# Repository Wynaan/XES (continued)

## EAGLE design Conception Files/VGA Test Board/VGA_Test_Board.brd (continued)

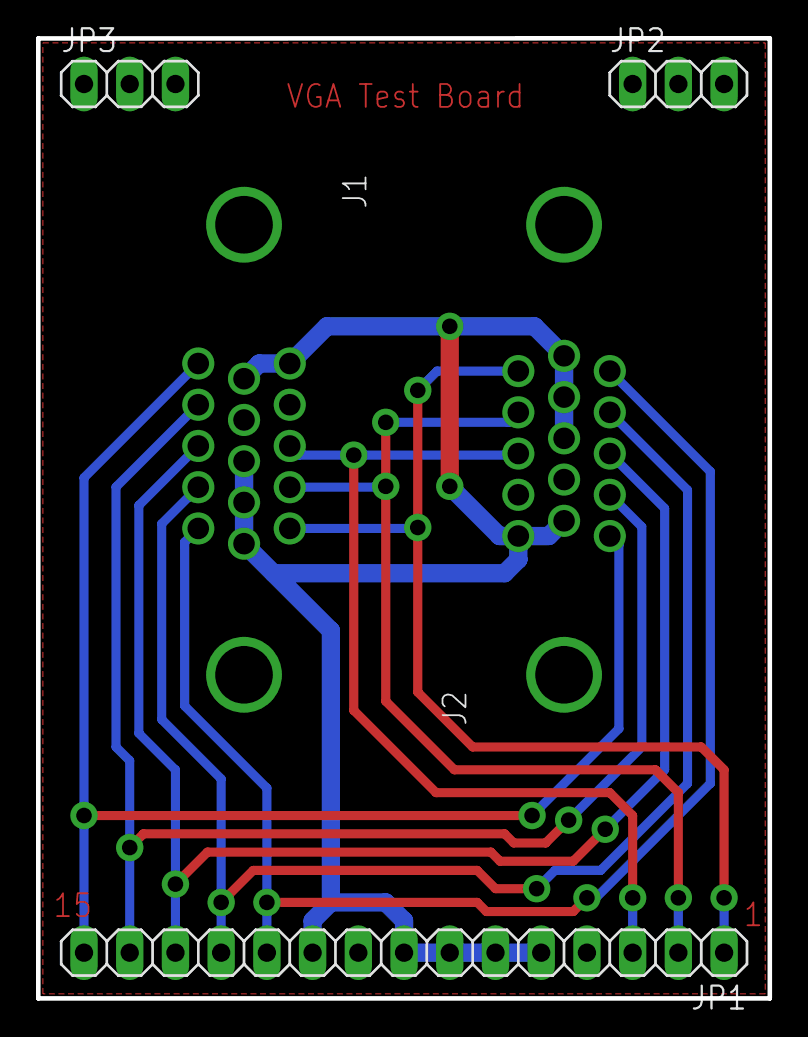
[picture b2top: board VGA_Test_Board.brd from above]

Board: 2 copper layers, 40.6 x 53.3 mm, 5 parts (0 on the bottom side), 9 nets.

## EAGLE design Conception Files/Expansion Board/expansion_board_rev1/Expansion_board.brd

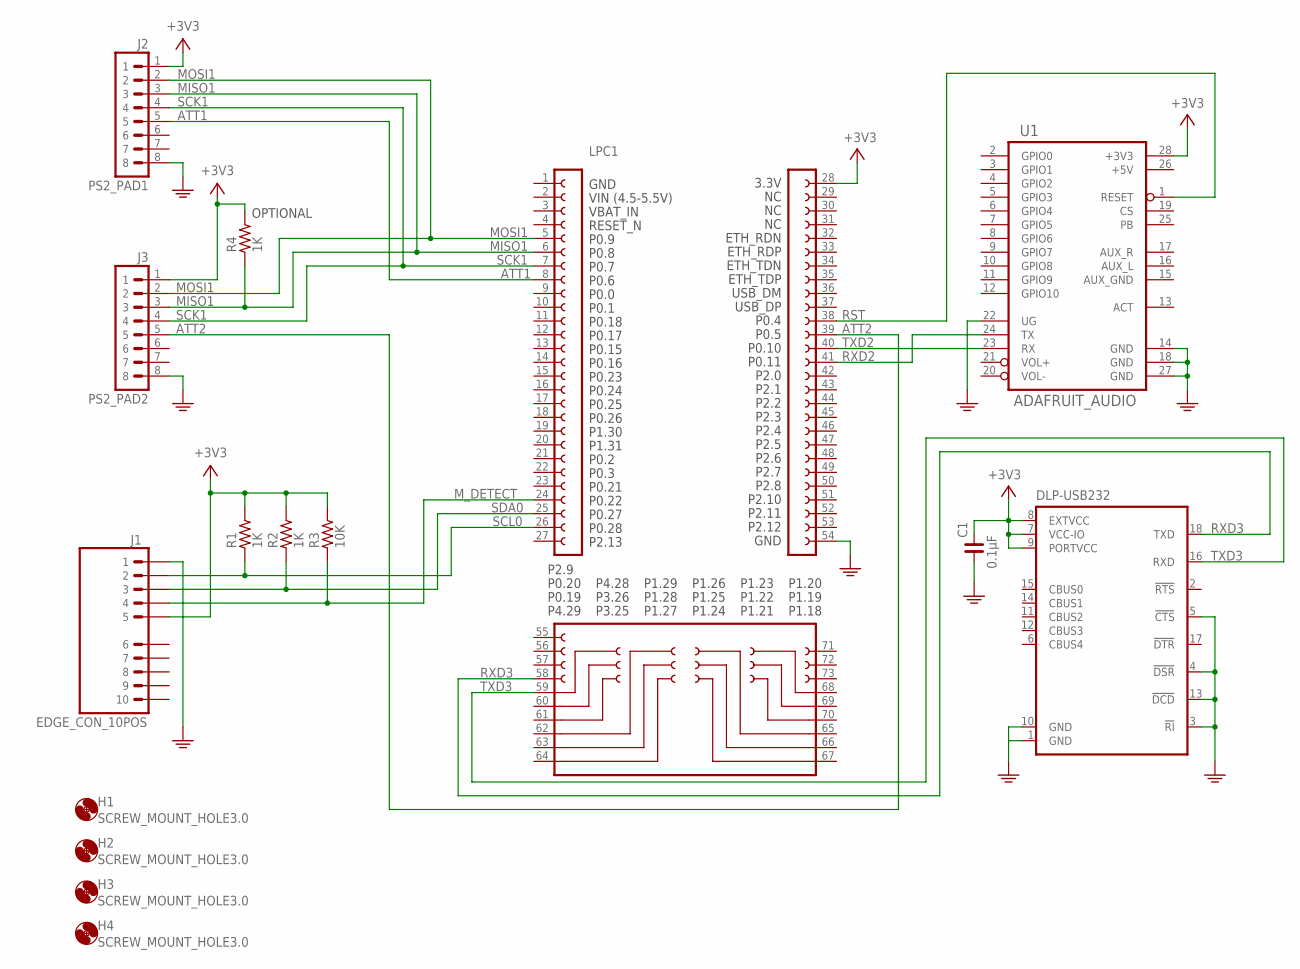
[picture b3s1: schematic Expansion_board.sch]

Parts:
C1: 0.1µF; C1206
H1, H2, H3, H4: SCREW_MOUNT_HOLE3.0; 3MM_HOLE
J1: EDGE_CON_10POS
J2: PS2_PAD1; MOLEX43045_0806
J3: PS2_PAD2; MOLEX43045_0806
LPC1: LPCXPRESSO_LPC1769
R1, R2, R4: 1K; R1206
R3: 10K; R1206
U1: ADAFRUIT_AUDIO; AUDIO_FX_SOUND_BOARD
U$1: DLP-USB232

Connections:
+3V3: C1.2, J1.5, J2.1, J3.1, LPC1.28, R1.2, R2.2, R3.2, R4.2, U1.28 (+3V3), U$1.7 (VCC-IO), U$1.8 (EXTVCC), U$1.9 (PORTVCC)
ATT1: J2.5, LPC1.8
ATT2: J3.5, LPC1.39
GND: C1.1, J1.1, J2.8, J3.8, LPC1.54, U1.14 (GND), U1.18 (GND), U1.22 (UG), U1.27 (GND), U$1.1 (GND), U$1.3 (!RI), U$1.4 (!DSR), U$1.5 (!CTS), U$1.10 (GND), U$1.13 (!DCD)
MISO1: J2.3, J3.3, LPC1.6, R4.1
MOSI1: J2.2, J3.2, LPC1.5
M_DETECT: J1.4, LPC1.24, R3.1
RST: LPC1.38, U1.1 (RESET)
RXD2: LPC1.41, U1.24 (TX)
RXD3: LPC1.58, U$1.18 (TXD)
SCK1: J2.4, J3.4, LPC1.7
SCL0: J1.2, LPC1.26, R1.1
SDA0: J1.3, LPC1.25, R2.1
TXD2: LPC1.40, U1.23 (RX)
TXD3: LPC1.59, U$1.16 (RXD)

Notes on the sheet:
OPTIONAL

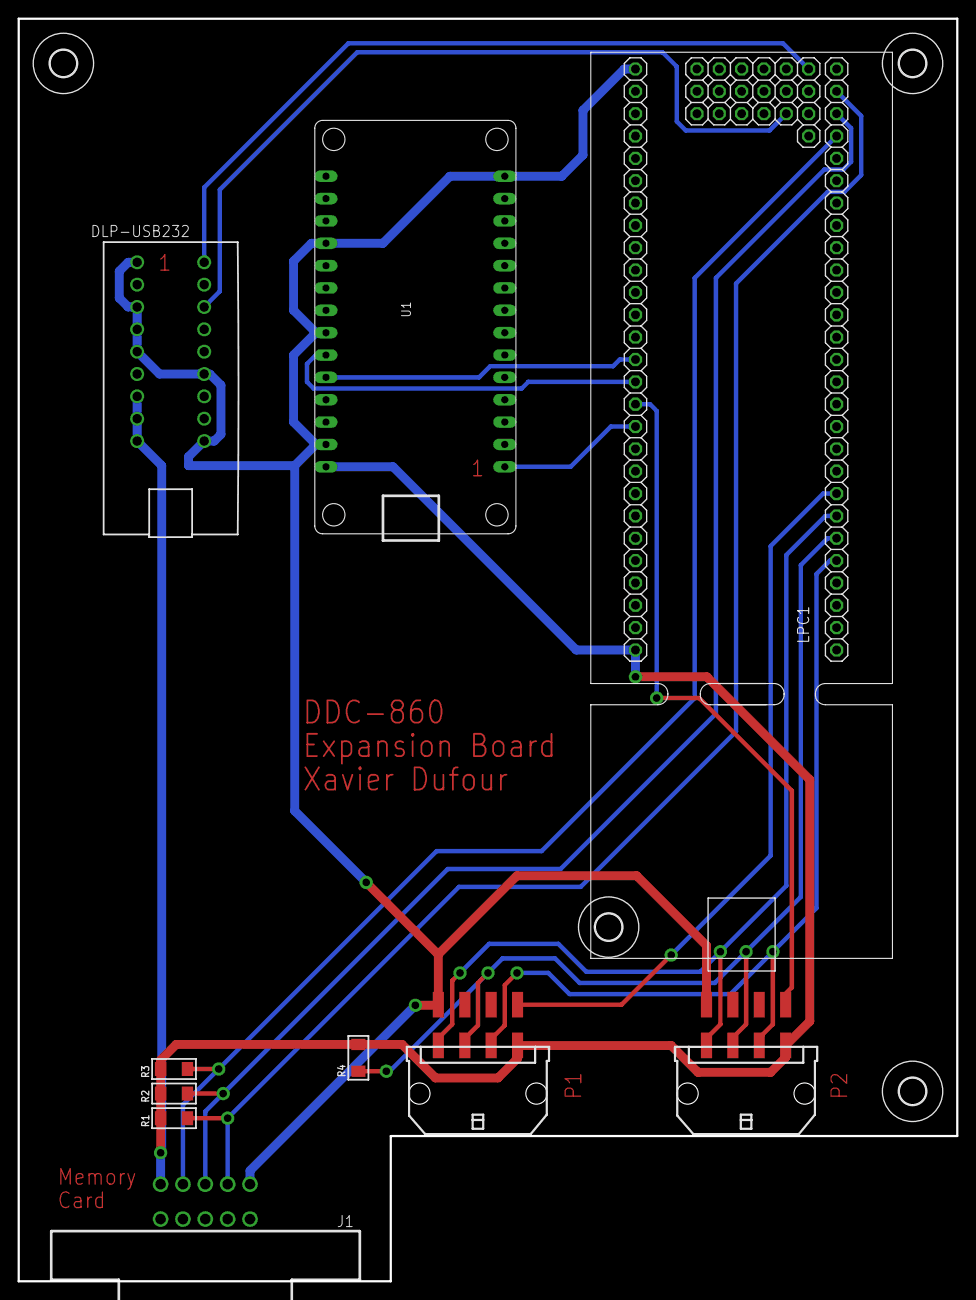
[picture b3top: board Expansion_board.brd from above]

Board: 2 copper layers, 106.7 x 143.5 mm, 15 parts (1 on the bottom side), 15 nets.

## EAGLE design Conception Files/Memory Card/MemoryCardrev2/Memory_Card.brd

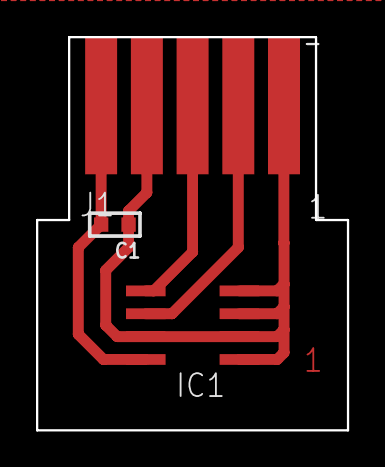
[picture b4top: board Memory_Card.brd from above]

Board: 2 copper layers, 17.3 x 21.8 mm, 3 parts (0 on the bottom side), 4 nets.

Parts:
C1: 0.1µF; C0603
IC1: 24LC256SN; SO-08
J1: EDGE_CON_PADS_10POS; EDGE_CON_PADS

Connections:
+3V3: C1.2, IC1.8, J1.5
GND: C1.1, IC1.1, IC1.2, IC1.3, IC1.4, IC1.7, J1.1, J1.4
SCL: IC1.6, J1.2
SDA: IC1.5, J1.3

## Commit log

2019-07-31 Uploaded last stable release
2020-03-08 Uploaded entire project documentation & production files
